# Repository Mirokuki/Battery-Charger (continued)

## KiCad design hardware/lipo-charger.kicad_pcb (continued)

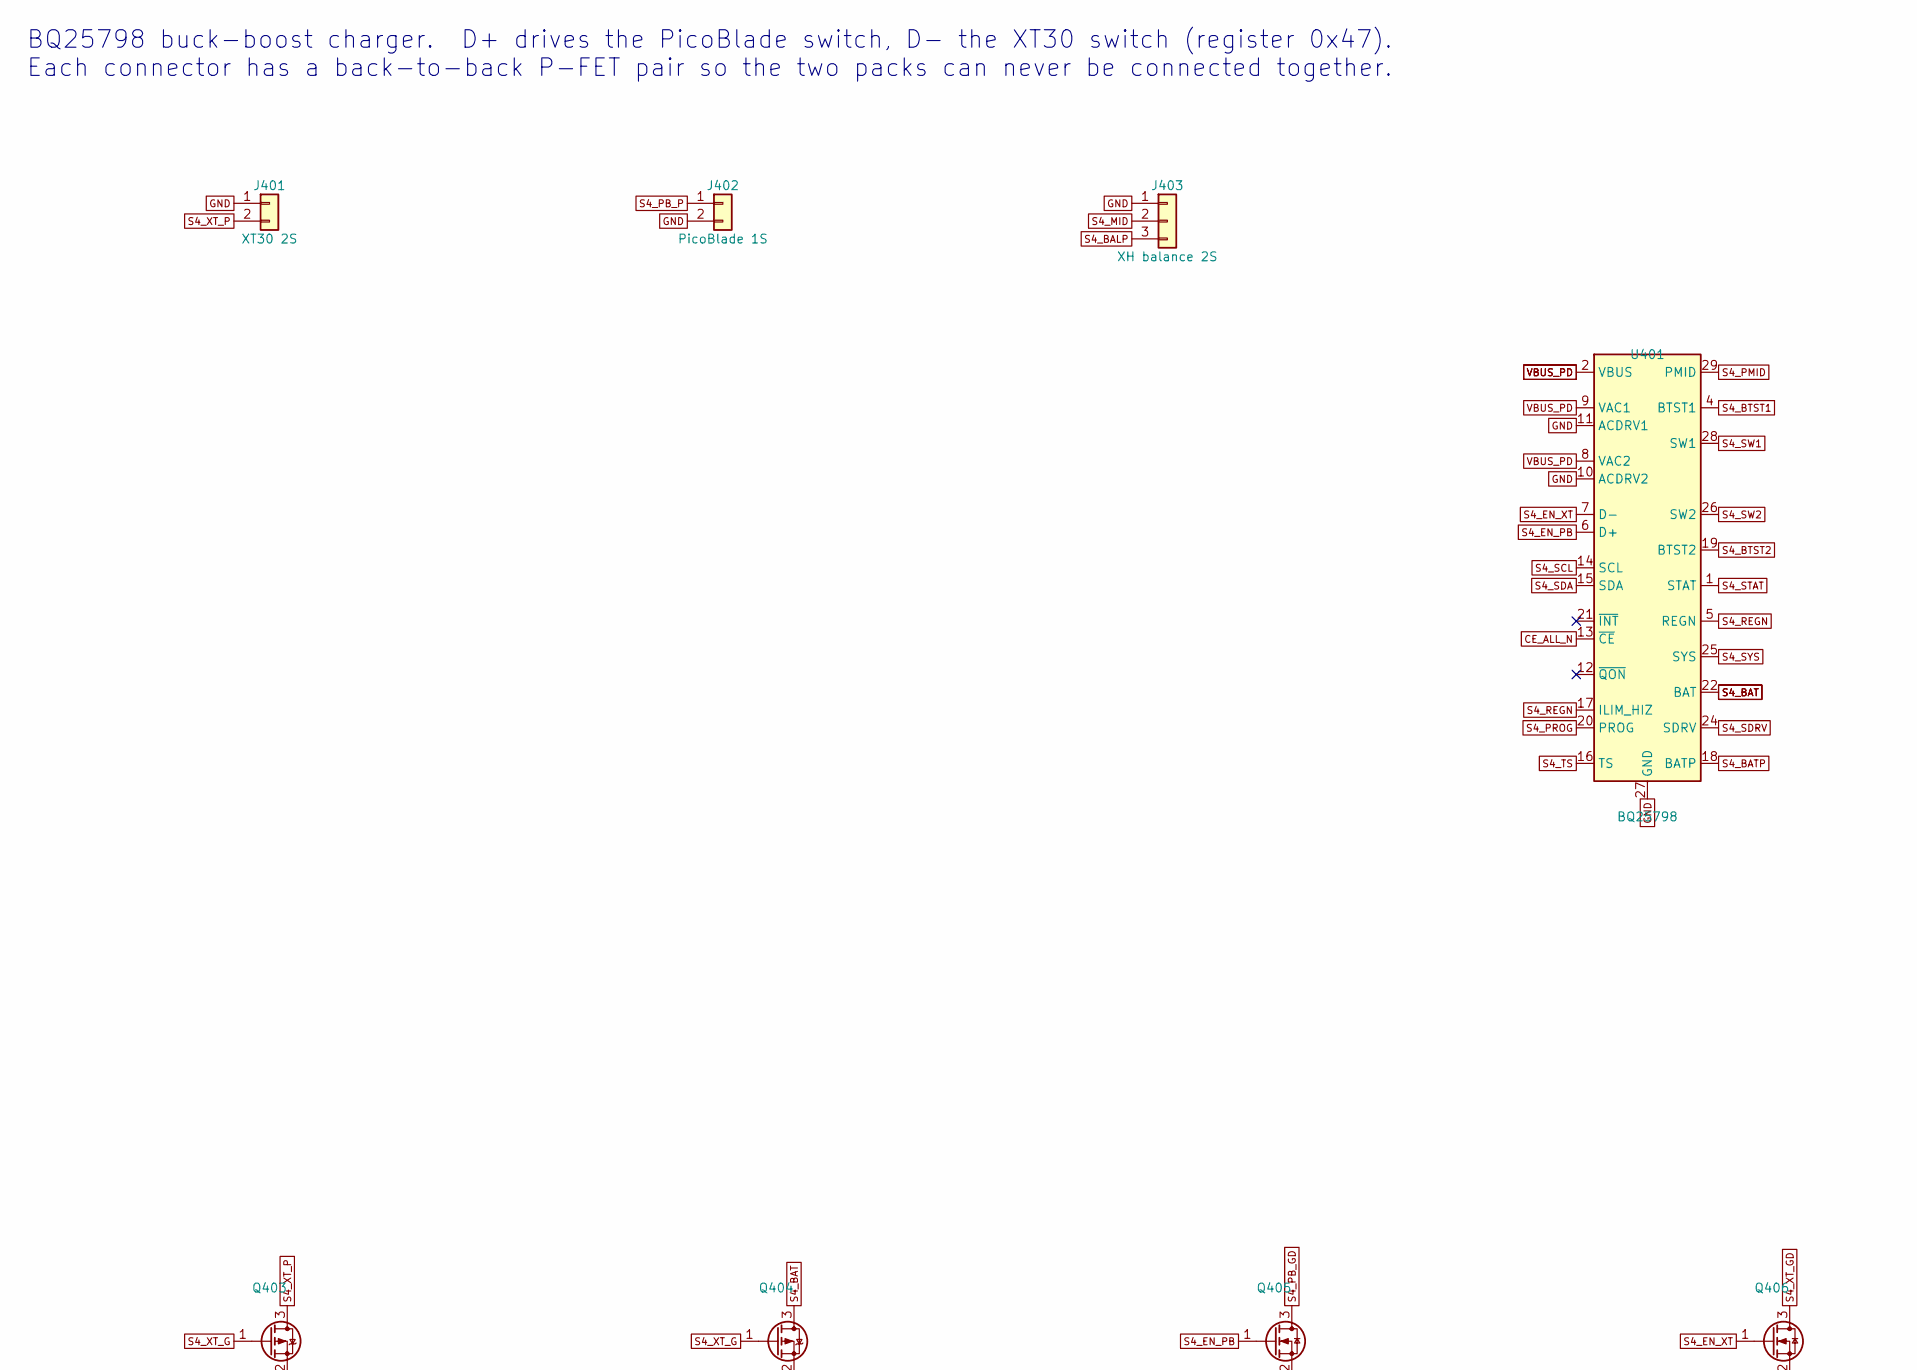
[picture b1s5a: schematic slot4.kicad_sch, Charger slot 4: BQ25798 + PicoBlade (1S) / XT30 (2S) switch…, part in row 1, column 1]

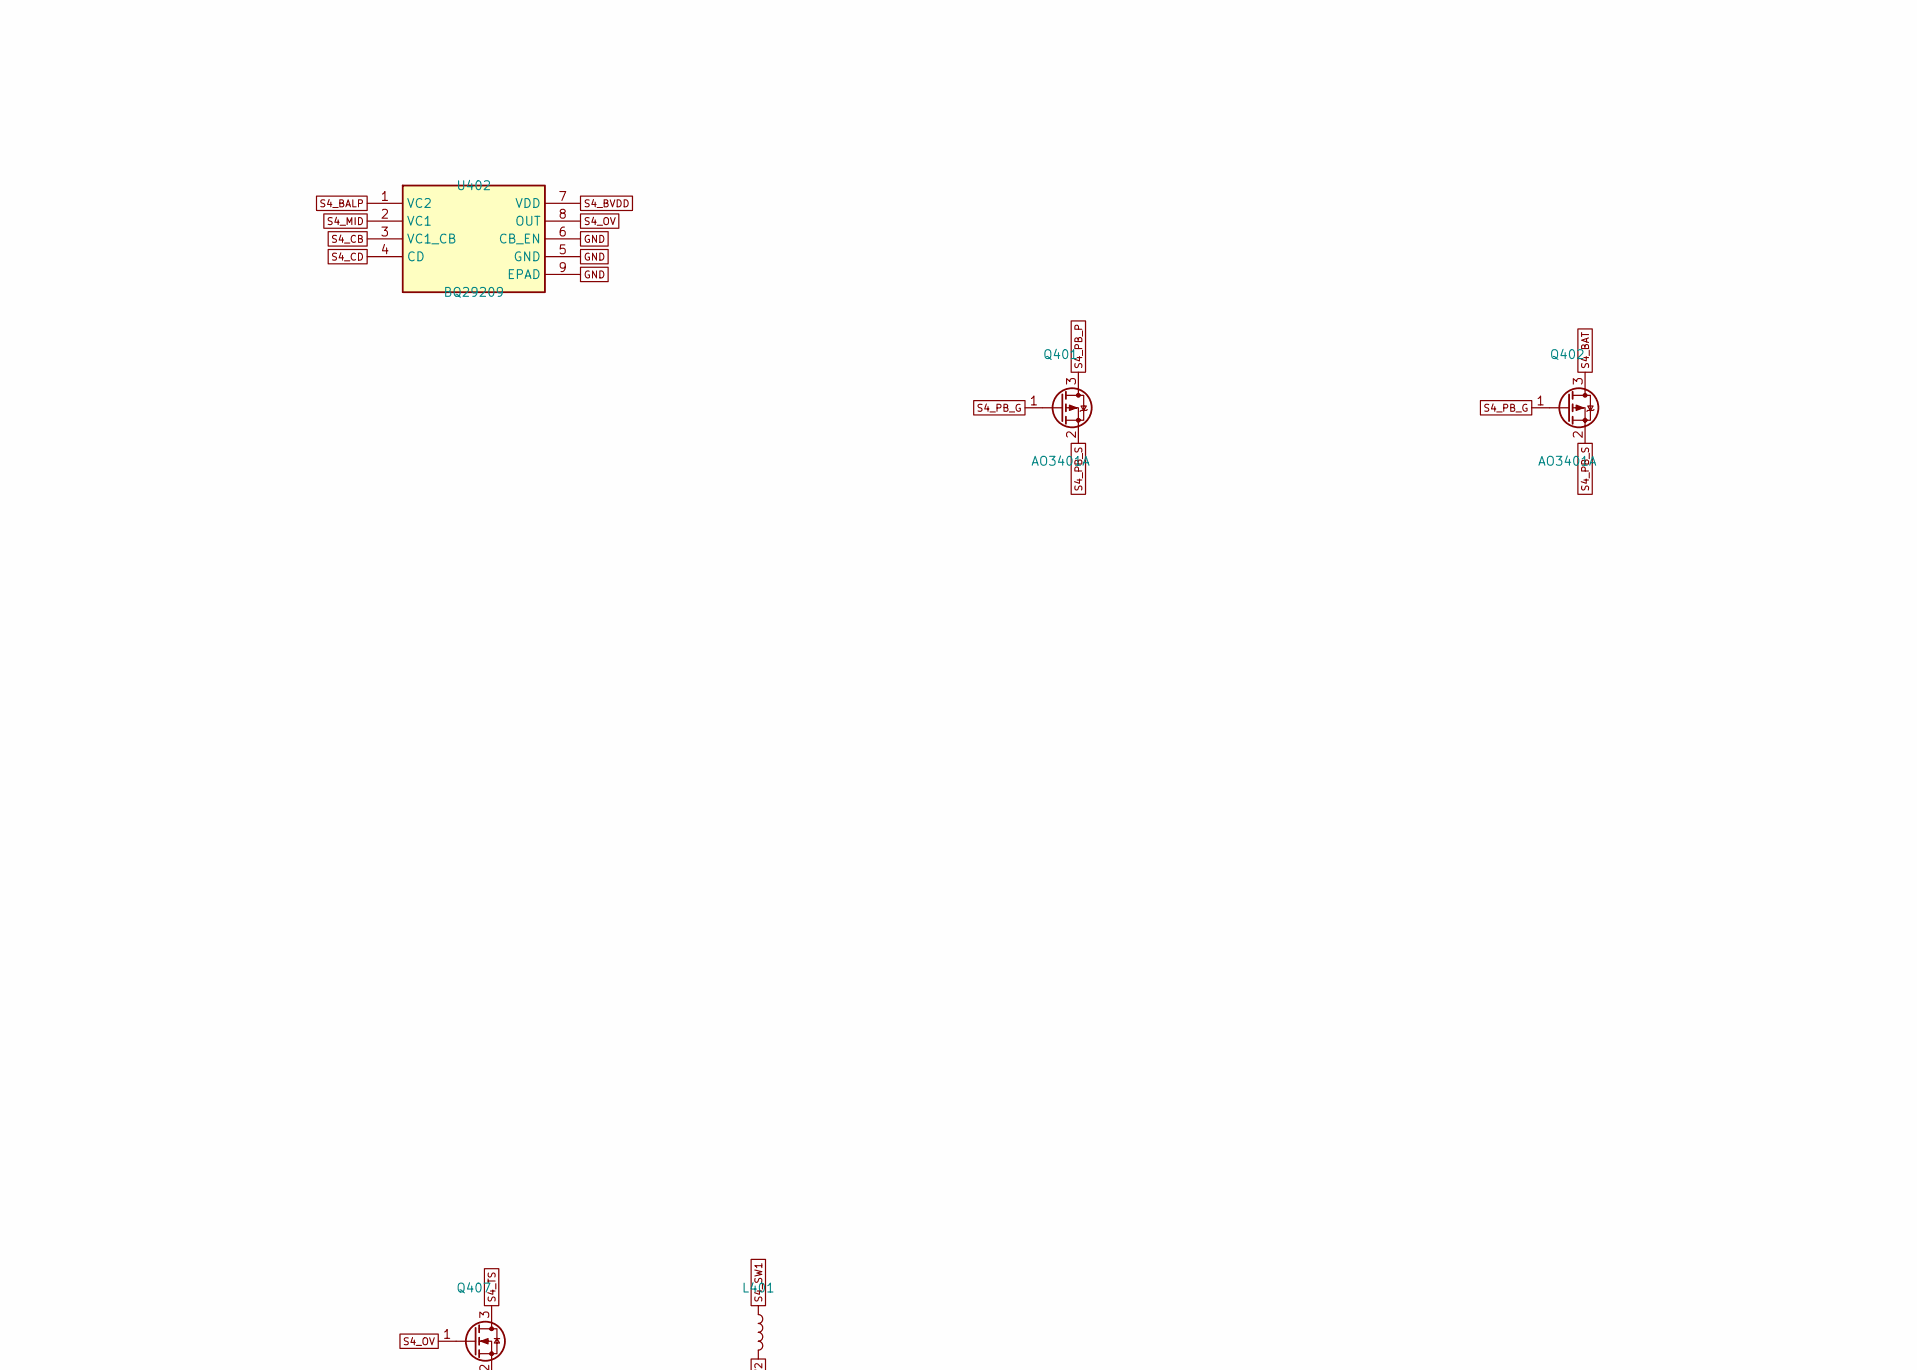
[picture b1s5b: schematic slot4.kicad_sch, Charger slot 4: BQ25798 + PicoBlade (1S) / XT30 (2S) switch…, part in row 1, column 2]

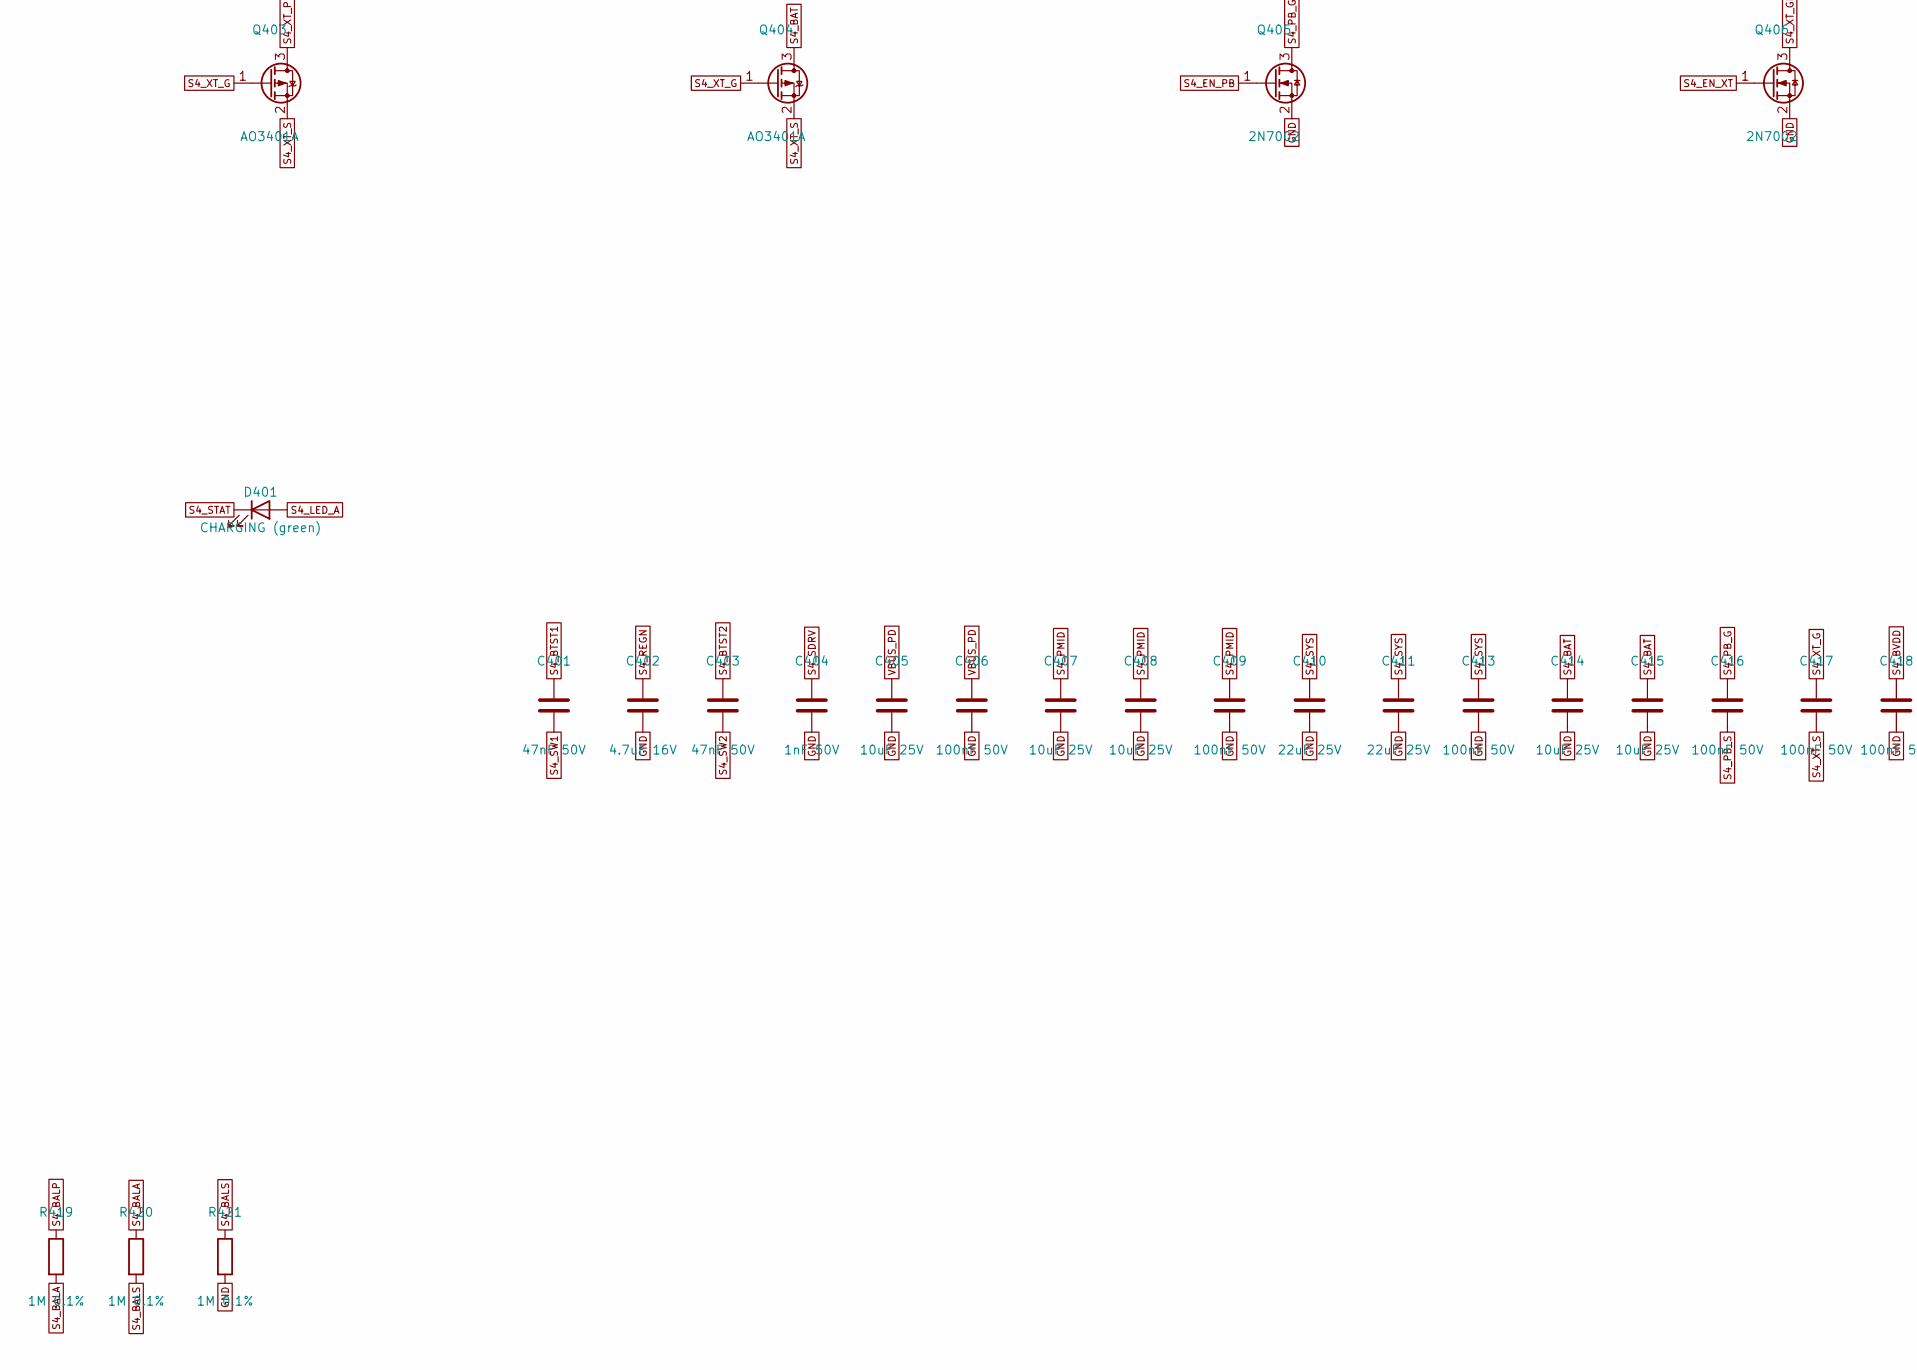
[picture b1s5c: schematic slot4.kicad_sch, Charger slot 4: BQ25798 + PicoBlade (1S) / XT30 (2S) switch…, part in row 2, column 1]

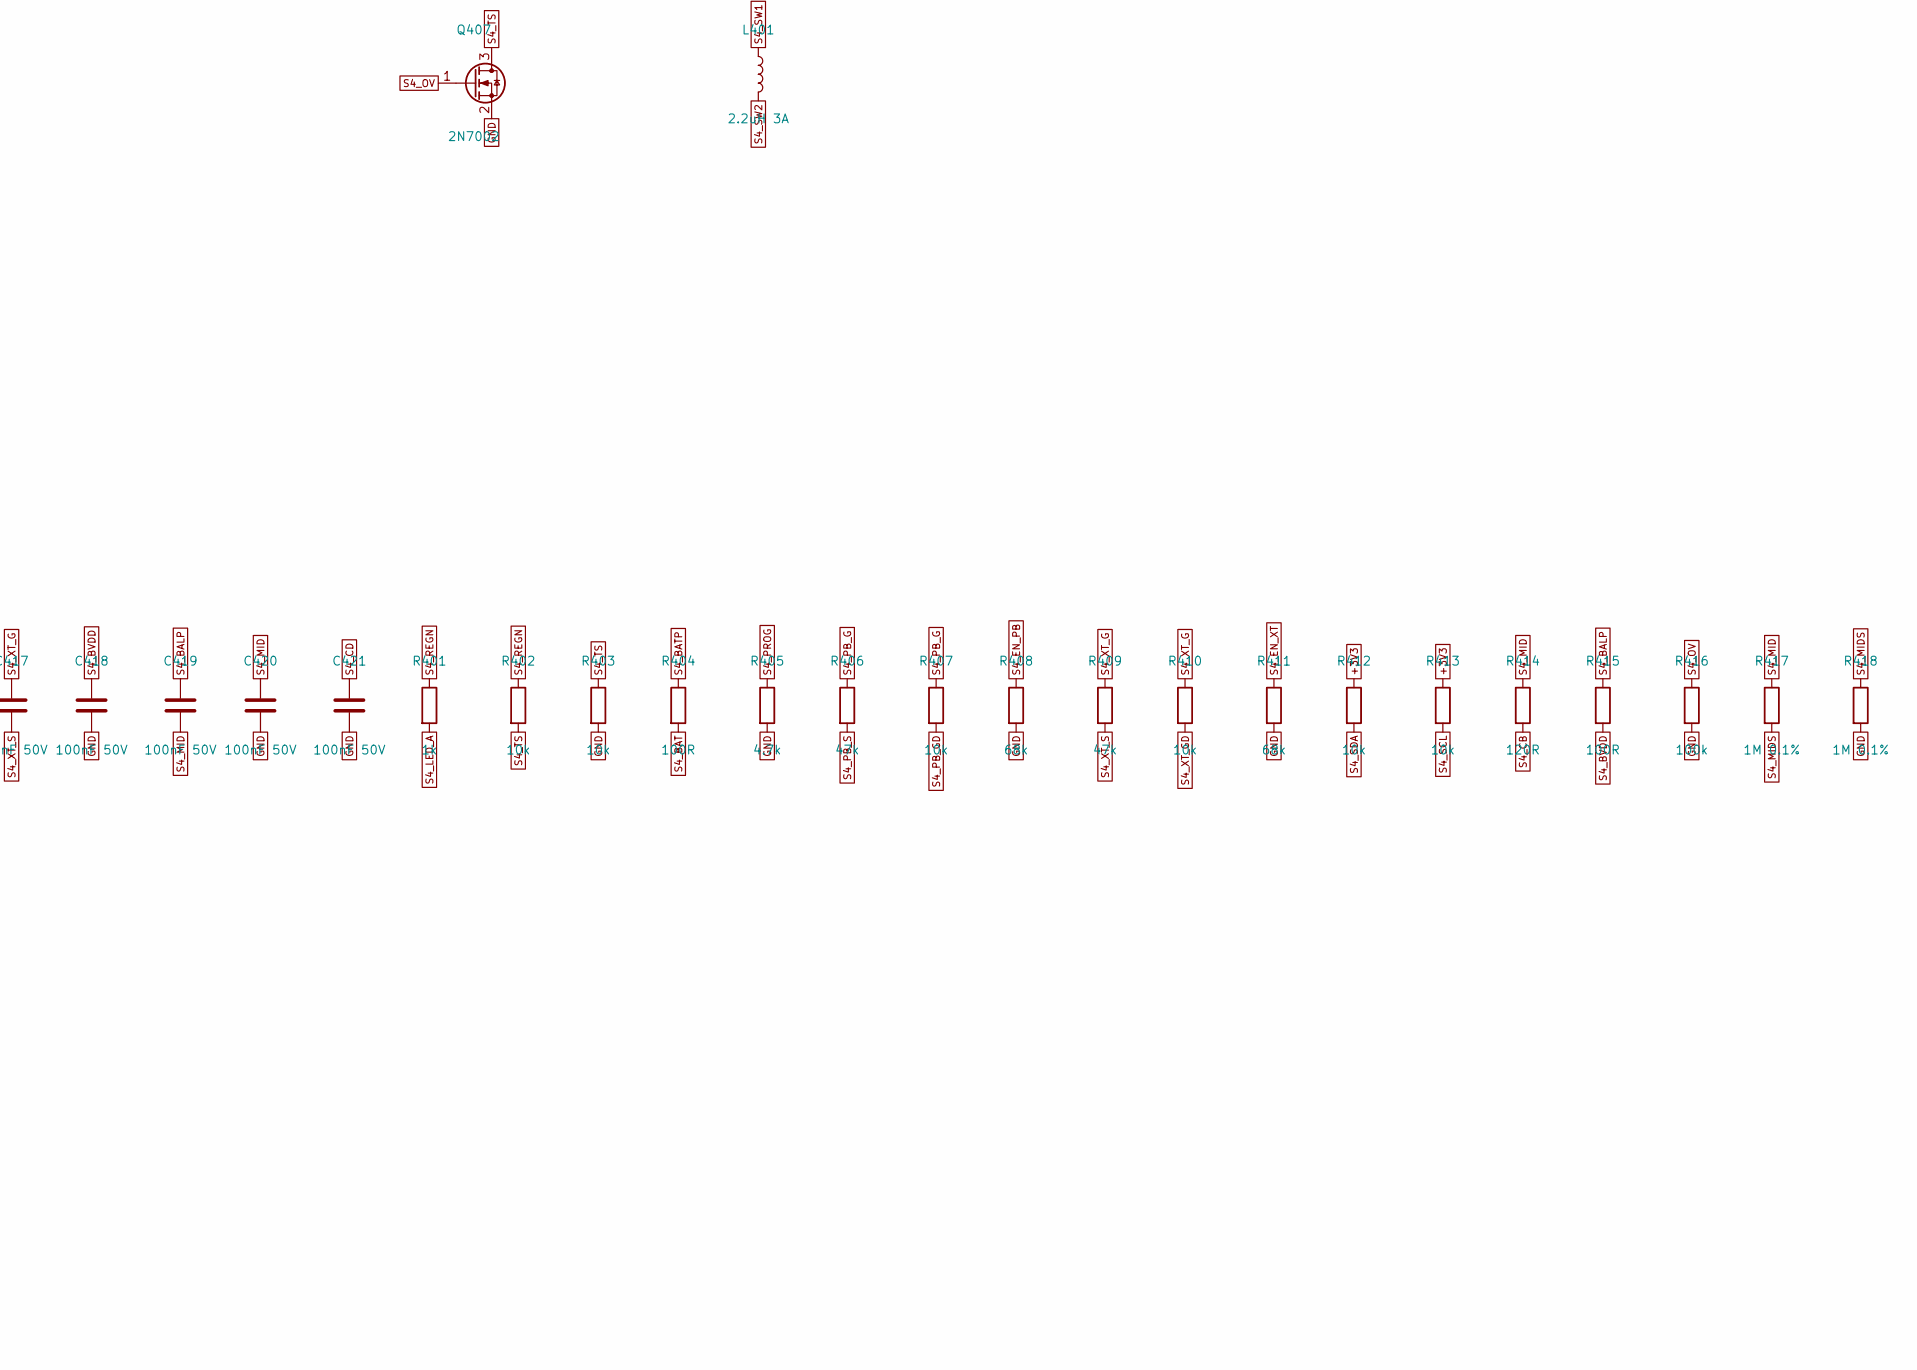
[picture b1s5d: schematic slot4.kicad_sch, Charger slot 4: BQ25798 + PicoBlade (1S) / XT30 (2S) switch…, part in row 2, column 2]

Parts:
C401, C403: 47nF 50V; C_0402_1005Metric; MPN CL05B473KB5NNNC
C402: 4.7uF 16V; C_0603_1608Metric; MPN CL10A475KO8NNNC; LCSC C19666
C404: 1nF 50V; C_0402_1005Metric; MPN CL05B102KB5NNNC; LCSC C1523
C405, C407, C408, C414, C415: 10uF 25V; C_0805_2012Metric; MPN CL21A106KAYNNNE; LCSC C15850
C406, C409, C413, C416, C417, C418, C419, C420, C421: 100nF 50V; C_0402_1005Metric; MPN CL05B104KB54PNC; LCSC C307331
C410, C411: 22uF 25V; C_0805_2012Metric; MPN CL21A226MAQNNNE; LCSC C45783
D401: CHARGING (green); LED_0603_1608Metric; MPN 19-217/GHC-YR1S2/3T; LCSC C72043
J401: XT30 2S; AMASS_XT30UPB-M_1x02_P5.0mm_Vertical; MPN XT30UPB-M; LCSC C99101
J402: PicoBlade 1S; Molex_PicoBlade_53047-0210_1x02_P1.25mm_Vertical; MPN 0530470210
J403: XH balance 2S; JST_XH_B3B-XH-A_1x03_P2.50mm_Vertical; MPN B3B-XH-A; LCSC C144394
L401: 2.2uH 3A; L_Changjiang_FNR4030S; MPN FNR4030S2R2MT
Q401, Q402, Q403, Q404: AO3401A; SOT-23; MPN AO3401A; LCSC C15127
Q405, Q406, Q407: 2N7002; SOT-23; MPN 2N7002; LCSC C8545
R401: 1k; R_0402_1005Metric; MPN 0402WGF1001TCE; LCSC C11702
R402, R403, R407, R410, R412, R413: 10k; R_0402_1005Metric; MPN 0402WGF1002TCE; LCSC C25744
R404, R415: 100R; R_0402_1005Metric; MPN 0402WGF1000TCE; LCSC C25076
R405: 4.7k; R_0402_1005Metric; MPN 0402WGF4701TCE; LCSC C25900
R406, R409: 47k; R_0402_1005Metric; MPN 0402WGF4702TCE; LCSC C25792
R408, R411: 68k; R_0402_1005Metric; MPN 0402WGF6802TCE; LCSC C36871
R414: 120R; R_0402_1005Metric; MPN 0402WGF1200TCE
R416: 100k; R_0402_1005Metric; MPN 0402WGF1003TCE; LCSC C25741
R417, R418, R419, R420, R421: 1M 0.1%; R_0402_1005Metric; MPN RT0402BRD071ML
U401: BQ25798; Texas_RQM0029A_VQFN-29_4x4mm_P0.4mm; MPN BQ25798RQMR; LCSC C2876768
U402: BQ29209; VSON-8-1EP_3x3mm_P0.65mm_EP1.65x2.4mm; MPN BQ29209DRBR

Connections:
+3V3: R412.1, R413.1; also elsewhere on the board
CE_ALL_N: U401.13 (~CE); also elsewhere on the board
GND: C402.2, C404.2, C405.2, C406.2, C407.2, C408.2, C409.2, C410.2, C411.2, C413.2, C414.2, C415.2, C418.2, C420.2, C421.2, J401.1, J402.2, J403.1, Q405.2 (S), Q406.2 (S), Q407.2 (S), R403.2, R405.2, R408.2, R411.2, R416.2, R418.2, R421.2, U401.10 (ACDRV2), U401.11 (ACDRV1), U401.27 (GND), U402.5 (GND), U402.6 (CB_EN), U402.9 (EPAD); also elsewhere on the board
S4_BALA: R419.2, R420.1
S4_BALP: C419.1, J403.3, R415.1, R419.1, U402.1 (VC2)
S4_BALS: R420.2, R421.1; also elsewhere on the board
S4_BAT: C414.1, C415.1, Q402.3 (D), Q404.3 (D), R404.2, U401.22 (BAT), U401.23 (BAT)
S4_BATP: R404.1, U401.18 (BATP)
S4_BTST1: C401.1, U401.4 (BTST1)
S4_BTST2: C403.1, U401.19 (BTST2)
S4_BVDD: C418.1, R415.2, U402.7 (VDD)
S4_CB: R414.2, U402.3 (VC1_CB)
S4_CD: C421.1, U402.4 (CD)
S4_EN_PB: Q405.1 (G), R408.1, U401.6 (D+)
S4_EN_XT: Q406.1 (G), R411.1, U401.7 (D-)
S4_LED_A: D401.2 (A), R401.2
S4_MID: C419.2, C420.1, J403.2, R414.1, R417.1, U402.2 (VC1)
S4_MIDS: R417.2, R418.1; also elsewhere on the board
S4_OV: Q407.1 (G), R416.1, U402.8 (OUT)
S4_PB_G: C416.1, Q401.1 (G), Q402.1 (G), R406.1, R407.1
S4_PB_GD: Q405.3 (D), R407.2
S4_PB_P: J402.1, Q401.3 (D)
S4_PB_S: C416.2, Q401.2 (S), Q402.2 (S), R406.2
S4_PMID: C407.1, C408.1, C409.1, U401.29 (PMID)
S4_PROG: R405.1, U401.20 (PROG)
S4_REGN: C402.1, R401.1, R402.1, U401.5 (REGN), U401.17 (ILIM_HIZ)
S4_SCL: R413.2, U401.14 (SCL); also elsewhere on the board
S4_SDA: R412.2, U401.15 (SDA); also elsewhere on the board
S4_SDRV: C404.1, U401.24 (SDRV)
S4_STAT: D401.1 (K), U401.1 (STAT)
S4_SW1: C401.2, L401.1, U401.28 (SW1)
S4_SW2: C403.2, L401.2, U401.26 (SW2)
S4_SYS: C410.1, C411.1, C413.1, U401.25 (SYS)
S4_TS: Q407.3 (D), R402.2, R403.1, U401.16 (TS)
S4_XT_G: C417.1, Q403.1 (G), Q404.1 (G), R409.1, R410.1
S4_XT_GD: Q406.3 (D), R410.2
S4_XT_P: J401.2, Q403.3 (D)
S4_XT_S: C417.2, Q403.2 (S), Q404.2 (S), R409.2
VBUS_PD: C405.1, C406.1, U401.2 (VBUS), U401.3 (VBUS), U401.8 (VAC2), U401.9 (VAC1); also elsewhere on the board

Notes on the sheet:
BQ25798 buck-boost charger. D+ drives the PicoBlade switch, D- the XT30 switch (register 0x47). Each connector has a back-to-back P-FET pair so the two packs can never be connected together.
